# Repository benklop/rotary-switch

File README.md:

# Rotary Light Switch

3D-printed single-gang US rotary light switch using an EC11 encoder and ESP32-S2 Mini, with a standard faceplate and knob. Control a dimmable/color light from Home Assistant: toggle, dim, hue, and color temperature. Optional RGB LED behind the knob for feedback or night light (controllable as a light in HA).

## Contents

- **openscad/** – Housing (single-gang, 2 3/8" faceplate screws, 3 9/32" box mount). No printed faceplate; use a standard toggle/rotary-dimmer plate.
- **esphome/** – ESPHome config for Lolin S2 Mini: rotary encoder + push button, exposed to Home Assistant.
- **homeassistant/blueprints/automation/** – Speed-sensitive RGB blueprints (`rotary_dimmer_rgb.yaml`, `rotary_dimmer_rgb_with_fan.yaml`): Encoder Speed sensor, Kelvin CT on the light, saturation-first hue mode. With the optional fan button configured, double-press is hue and the fan button toggles fan; without it, double-press toggles fan mode. See [homeassistant/blueprints/automation/README.md](homeassistant/blueprints/automation/README.md).
- **docs/** – Wiring, BOM, assembly.

## Quick start

1. Print the housing (`openscad/`), flash ESPHome (`esphome/`), wire encoder and PSU (see [docs/wiring.md](docs/wiring.md)).
2. Mount encoder, boards, and knob in the housing; install in the wall with a standard faceplate.
3. In Home Assistant, add the device, create the helpers for your blueprint (mode input_select, hue sub-mode select for RGB blueprints, optional fan button entity, 30 s timer — see [homeassistant/blueprints/automation/README.md](homeassistant/blueprints/automation/README.md)), then create an automation from `rotary_dimmer_rgb.yaml` or `rotary_dimmer_rgb_with_fan.yaml`.

See [docs/assembly.md](docs/assembly.md) and [docs/bom.md](docs/bom.md) for full steps and parts.

## Hardware

- EC11 rotary encoder (15 mm shaft, **splined** 6 mm)
- ESP32-S2 Mini (Lolin S2 Mini), [pinout](https://done.land/components/microcontroller/families/esp/esp32/developmentboards/esp32-s2/s2mini/)
- WX-DC12003 5 V 700 mA PSU (23.5×18.1 mm)
- Lutron knob (5.5 mm split-shaft type; heat and form to fit 6 mm splined encoder—see docs); standard single-gang faceplate

## License

Use and modify as you like; no warranty.

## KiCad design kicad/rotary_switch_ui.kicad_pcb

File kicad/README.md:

## KiCad: Rotary switch UI PCB

This folder contains a small PCB intended to mount:

- An **EC11/EC11E-style rotary encoder with push switch**
- A **5 mm through-hole common-cathode RGB LED**
- **3× current-limit resistors** for the LED
- A **1×8 2.54 mm header** for wiring to the ESP32-S2 Mini

### Project files

- `rotary_switch_ui.kicad_pro`
- `rotary_switch_ui.kicad_sch`
- `rotary_switch_ui.kicad_pcb`

### Mechanical reference

The PCB footprint placement is aligned to the OpenSCAD model:

- **Encoder center** at `(0, 0)` mm
- **LED center** at `(0, -9.5)` mm (from `openscad/dimensions.scad` `led_offset_y`)

### Recommended footprints (to assign in schematic)

If you open the schematic and run **Update PCB from Schematic**, assign these footprints first so KiCad can match by reference designator:

- `SW1` (encoder): `Rotary_Encoder:RotaryEncoder_Alps_EC11E-Switch_Vertical_H20mm`
- `D1` (LED): `LED_THT:LED_D5.0mm-4_RGB`
- `R1`, `R2`, `R3` (resistors): `Resistor_SMD:R_0805_2012Metric` (or switch to THT if preferred)
- `J1` (to ESP32): `Connector_PinHeader_2.54mm:PinHeader_1x08_P2.54mm_Vertical`

### Header pinout (J1)

1. `+3V3` (optional; typically not needed for a bare EC11)
2. `GND`
3. `ENC_A` (encoder A → ESP32 GPIO34 per `docs/wiring.md`)
4. `ENC_B` (encoder B → ESP32 GPIO36)
5. `ENC_BTN` (push button → ESP32 GPIO37)
6. `LED_R_IN` (→ R1 → LED_R; ESP32 GPIO4)
7. `LED_G_IN` (→ R2 → LED_G; ESP32 GPIO5)
8. `LED_B_IN` (→ R3 → LED_B; ESP32 GPIO6)

# Rotary front panel PCB

Small PCB to mount the EC11 encoder, 5 mm RGB LED, and current-limiting resistors for the [rotary light switch](../README.md) project. Connects to the ESP32-S2 Mini via a 8-pin header.

## Contents

- **rotary-front.kicad_pro** – KiCad 8 project
- **rotary-front.kicad_pcb** – Board with footprints placed (encoder, LED, 3× 0805 resistors, 1×8 pin header). No schematic yet; create one and then **Update PCB from Schematic**.

## Schematic (create in Eeschema)

Create a new schematic in this project and add:

| Ref | Symbol / part | Footprint | Value / notes |
|-----|----------------|-----------|----------------|
| U1 | **Device:RotaryEncoder_Switch** | **Rotary_Encoder:RotaryEncoder_Alps_EC11E-Switch_Vertical_H20mm** | EC11 with switch |
| D1 | **LED:LED_RGB_CommonCathode** or 4-pin connector | **LED_THT:LED_D5.0mm-4_RGB** | 5 mm common-cathode RGB |
| R1 | **Device:R** | **Resistor_SMD:R_0805_2012Metric** | **470 Ω** (red channel) |
| R2 | **Device:R** | **Resistor_SMD:R_0805_2012Metric** | **430 Ω** (green) |
| R3 | **Device:R** | **Resistor_SMD:R_0805_2012Metric** | **430 Ω** (blue) |
| J1 | **Connector:Conn_01x08** | **Connector_PinHeader_2.54mm:PinHeader_1x08_P2.54mm_Vertical** | To ESP32 |

### Net list (wire to J1)

Use these net names so the PCB matches [../docs/wiring.md](../docs/wiring.md):

| J1 pin | Net name   | ESP32-S2 Mini |
|--------|------------|----------------|
| 1      | +3V3 (opt) | 3V3 |
| 2      | GND        | GND |
| 3      | ENC_A      | GPIO 34 |
| 4      | ENC_B      | GPIO 36 |
| 5      | ENC_BTN    | GPIO 37 |
| 6      | LED_R_IN   | GPIO 4 (via R1 470 Ω) |
| 7      | LED_G_IN   | GPIO 5 (via R2 430 Ω) |
| 8      | LED_B_IN   | GPIO 6 (via R3 430 Ω) |

- Connect **encoder** pins to ENC_A, ENC_B, ENC_BTN, and GND (check your EC11 datasheet for pin order; Alps EC11E footprint uses A, B, C, S1, S2 — map A/B/S1/S2 to ENC_A/ENC_B/ENC_BTN and GND as appropriate; no VCC is required for the encoder itself).
- Connect **LED** common cathode to **GND**; connect R, G, B anodes to the **R**, **G**, **B** nets (i.e. through R1, R2, R3 to the same-named J1 pins). Verify 5 mm RGB pinout (common cathode vs anode, R/G/B order) from your LED datasheet.

Then: **Tools → Assign footprint symbols**, assign the footprints above, **File → Update PCB from Schematic**, and in PCB Editor route the nets (or use the existing placement).

## PCB layout

- **Board size:** 50 mm × 35 mm (Edge.Cuts).
- **Encoder** at top center (shaft position aligned with front-panel 6 mm hole when the board is mounted).
- **LED** below the encoder (matches `led_offset_y = -9.5 mm` in the OpenSCAD dimensions).
- **J1** at bottom for cable to ESP32.

If your front panel or enclosure differs, move footprints in PCB Editor and adjust Edge.Cuts as needed.

## BOM (per board)

| Ref | Part | Value / spec |
|-----|------|----------------|
| U1 | Alps EC11 or compatible rotary encoder with switch, vertical, 6 mm shaft | 15 mm shaft, splined |
| D1 | 5 mm RGB LED, common cathode | 4-pin |
| R1 | Resistor 0805 | **470 Ω** |
| R2 | Resistor 0805 | **430 Ω** |
| R3 | Resistor 0805 | **430 Ω** |
| J1 | Pin header 1×8, 2.54 mm | Straight, THT |

## Manufacturing

- Single-sided (or two-layer) 1.6 mm FR4; 0.2 mm min trace/space is fine.
- After assembly, mount the PCB behind the 3D-printed front face with the encoder shaft through the 7 mm hole and the LED in the LED cavity; then follow the main [assembly](../docs/assembly.md) for wiring to the ESP32 and PSU.

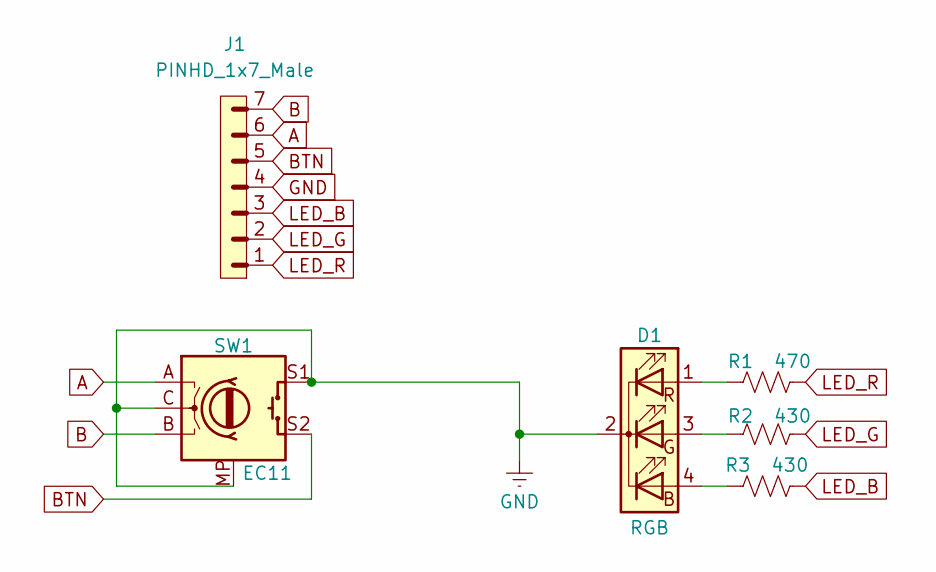
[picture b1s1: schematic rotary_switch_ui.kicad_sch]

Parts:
D1: RGB; LED_D5.0mm-4_RGB
J1: PINHD_1x7_Male; PinHeader_1x07_P2.54mm_Vertical
R1: 470; R_Axial_DIN0207_L6.3mm_D2.5mm_P7.62mm_Horizontal
R2, R3: 430; R_Axial_DIN0207_L6.3mm_D2.5mm_P7.62mm_Horizontal
SW1: EC11; RotaryEncoder_Alps_EC11E-Switch_Vertical_H20mm

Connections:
A: J1.6, SW1.A
B: J1.7, SW1.B
BTN: J1.5, SW1.S2
GND: D1.2 (K), J1.4, SW1.C, SW1.MP, SW1.S1
LED_B: J1.3, R3.2
LED_G: J1.2, R2.2
LED_R: J1.1, R1.2
unnamed: D1.4 (BA), R3.1
unnamed: D1.3 (GA), R2.1
unnamed: D1.1 (RA), R1.1

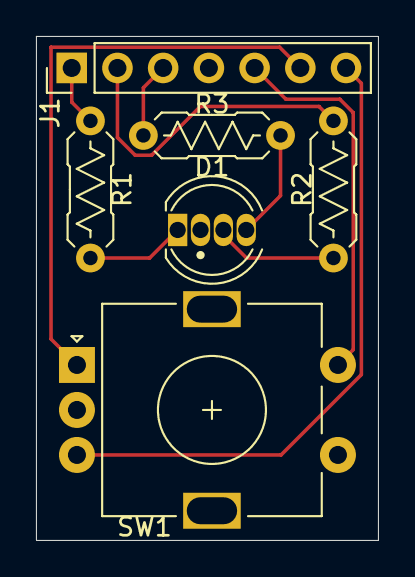
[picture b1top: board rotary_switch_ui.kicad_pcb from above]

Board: 2 copper layers, 19.0 x 28.0 mm, 6 parts (0 on the bottom side), 10 nets.

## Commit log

2026-02-26 Add initial project files for Rotary Light Switch
    - Created .gitignore to exclude build artifacts and sensitive files.
    - Added README.md with project overview, contents, quick start guide, and hardware specifications.
    - Included assembly instructions in docs/assembly.md.
    - Provided a bill of materials in docs/bom.md.
    - Documented wiring details in docs/wiring.md.
    - Added ESPHome configuration in esphome/rotary-lightswitch.yaml.
2026-02-27 Refactor assembly and wiring documentation for Rotary Light Switch
    Add a PCB for mounting the LED and the encoder
2026-02-27 Enhance Rotary Light Switch functionality and automation
    - Added encoder speed sensor to ESPHome configuration for improved responsiveness.
    - Implemented speed-based adjustments for brightness, hue, and color temperature in Home Assistant blueprints.
    - Introduced thresholds and multipliers for fine-tuning speed sensitivity in automation scripts.
2026-02-27 Update Rotary Dimmer Light automation and configuration
    - Modified entity descriptions in the automation blueprint for clarity.
    - Changed entity domain from `text_sensor` to `sensor` for encoder direction and button action entities.
    - Corrected value templates in automation actions to properly reference input entities.
    - Added a new package file for rotary dimmer light configuration, including input select and timer for mode management.
    - Implemented automation logic for rotary encoder actions, including mode switching and light control based on button presses.
2026-02-27 Refine Rotary Dimmer Light automation logic and entity definitions
    - Updated entity descriptions for clarity and consistency.
    - Changed entity domain from `text_sensor` to `sensor` for encoder direction and button action entities.
    - Corrected value templates in automation actions to properly reference input entities, ensuring accurate functionality for mode switching and light control.
2026-02-27 Refactor Rotary Dimmer Light automation for improved variable handling and logic consistency
    - Introduced new variable definitions for light, fan, and mode selection to streamline automation logic.
    - Updated value templates to reference defined variables instead of input entities, enhancing readability and maintainability.
    - Ensured consistent handling of brightness, hue, and color temperature adjustments based on encoder speed and thresholds.
2026-02-27 simplify
2026-02-27 Refactor Rotary Lightswitch configuration and automation for CW/CCW functionality
    - Updated ESPHome configuration to simplify encoder handling by replacing delta degrees with binary sensors for clockwise and counterclockwise actions.
    - Adjusted resolution for encoder steps to improve responsiveness.
    - Modified Home Assistant automation blueprint to utilize new binary sensors, enhancing clarity and functionality for light dimming based on encoder rotation.
    - Improved variable definitions and descriptions for better maintainability and understanding.
2026-02-27 Fix timing configuration in Rotary Lightswitch YAML to correct ON duration from 0. qqqqqqq5s to 0.5s, ensuring proper functionality of the binary sensor automation.
2026-03-20 try another approach
2026-03-20 Add reverse rotation option and adjust transition time default in Rotary Dimmer Light automation
2026-03-20 OGS-1654
2026-03-20 revert
2026-03-21 Add rotary dimmer RGB with fan automation blueprint and update helper package
    - Introduced a new automation blueprint for controlling a dimmable light and fan using a rotary encoder, allowing for speed-sensitive adjustments in brightness, fan speed, and color temperature.
    - Updated the helper package to support the new blueprint, removing the previous rotary dimmer light automation and simplifying the configuration for user-friendly setup.
2026-03-21 Refactor rotary dimmer automation blueprints for speed-sensitive RGB control
    - Updated rotary dimmer automation blueprint to enhance functionality for RGB color lights, including speed-sensitive brightness adjustments based on encoder rotation speed.
    - Added new parameters for slow, medium, and fast thresholds for brightness, hue, and color temperature adjustments.
    - Improved user experience with detailed behavior descriptions and optional feedback LED configurations.
    - Introduced a separate blueprint for rotary dimmer with fan control, allowing independent fan speed adjustments and mode toggling.
    - Enhanced documentation and descriptions for clarity on usage and configuration.
2026-03-21 Add rotary dimmer RGB blueprint with enhanced hue control and saturation adjustments
    - Introduced a new blueprint for rotary dimmer RGB control, allowing for speed-sensitive adjustments in brightness, hue, and color temperature.
    - Added input select helpers for hue sub-mode and saturation step sizes, improving user customization options.
    - Updated behavior descriptions to clarify functionality in different modes, including detailed interactions for single and double presses.
    - Enhanced documentation for setup and usage, ensuring a better user experience.
2026-03-21 Add long press functionality to rotary lightswitch for immediate color temperature mode activation
    - Implemented a new script to handle long press actions on the rotary encoder button, allowing for immediate entry into color temperature mode after a 500 ms hold.
    - Updated the binary sensor configuration to trigger the long press script on button press and stop it on release, enhancing responsiveness.
    - Revised documentation to reflect changes in long press behavior and its impact on automation interactions.
2026-03-21 correct if condition indentation
2026-03-21 Update README and documentation for rotary dimmer RGB blueprints and remove legacy blueprints
    - Revised README to reflect changes in rotary dimmer RGB blueprints, including new speed-sensitive features and detailed behavior descriptions for light and fan control.
    - Updated assembly documentation to clarify helper creation and automation setup for the new blueprints.
    - Removed outdated blueprints for rotary dimmer light and light with fan, consolidating functionality into the new rotary dimmer RGB blueprints.
    - Enhanced descriptions for input selects and behavior in the blueprints, ensuring a clearer understanding of user interactions.
2026-03-21 Enhance rotary dimmer RGB blueprints with optional night light feature
    - Added a new knob night light feature that activates a soft orange glow when the main light is off and the sun is below the horizon, improving usability in low-light conditions.
    - Updated descriptions for the knob LED behavior in normal and hue modes to reflect the new night light functionality.
    - Introduced new input parameters for night light brightness and enabled conditions for triggering the night light based on the state of the main light and sun position.
    - Refined automation actions to incorporate the night light feature, ensuring it operates seamlessly with existing functionalities.
2026-03-21 Refactor rotary dimmer blueprints for improved entity resolution and documentation
    - Updated rotary dimmer RGB blueprints to automatically resolve encoder, button, and knob LED entities from the selected ESPHome device, simplifying user setup.
    - Revised README and documentation to clarify the new entity resolution process and the importance of re-creating automations after blueprint upgrades.
    - Enhanced input parameters for rotary devices, including options for knob LED feedback, ensuring better integration and usability.
    - Streamlined automation actions to utilize the new entity resolution, improving overall functionality and user experience.
2026-03-21 Enhance rotary lightswitch functionality with idle timeout and mode management
    - Added an idle timeout feature to the rotary lightswitch, allowing automatic return to normal mode after a specified duration of inactivity.
    - Implemented new select options for rotary mode and hue adjustments, improving user control over light settings.
    - Introduced scripts for managing mode transitions and idle states, enhancing responsiveness and usability.
    - Updated documentation to reflect changes in functionality and setup requirements for the rotary lightswitch.
2026-03-21 Fix rotary lightswitch condition checks to use current_option for mode evaluation
    - Updated condition checks in the rotary lightswitch configuration to utilize `current_option()` instead of `state` for determining the current mode.
    - Ensured consistency in mode evaluation logic across scripts, enhancing reliability in mode transitions and actions.
2026-03-21 Refactor rotary dimmer automation for streamlined speed-sensitive adjustments
    - Simplified brightness, hue, saturation, fan speed, and kelvin adjustments in the rotary dimmer blueprints by consolidating conditional logic into a single speed tier index.
    - Enhanced code readability and maintainability by utilizing array indexing for step values based on speed tiers, improving overall functionality and user experience.
